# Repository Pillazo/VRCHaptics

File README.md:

# VRCHaptics
 VRC Haptics
A haptics set of software and hardware to give haptic feedback to VRChat on more than just your controllers. Old version used a melon-loader side-loaded dll file to pull bone positions out and set haptics. New version now uses the approved OSC system, by setting up the avatar in unity with 'VRC Contact Recievers'. A VB.NET program then grabs the OSC commands and then determines to turn on or off vibrating nodes you've mounted to yourself wherever!

A working example video here: https://youtu.be/_tgKSILLgIA

Node Assembly Video: https://youtu.be/x2D46sjlmms

Controller Assembly Video: https://youtu.be/UboYsb8L9xo

Controller Overview and use: https://youtu.be/rSFWYQzmyZ4

VB.Net program and use: https://youtu.be/C1V2dHkt9lk

Adding the Udon to your world: https://youtu.be/wW_y7pmaBFk

Find my project's discord at https://discord.gg/QjyNznq

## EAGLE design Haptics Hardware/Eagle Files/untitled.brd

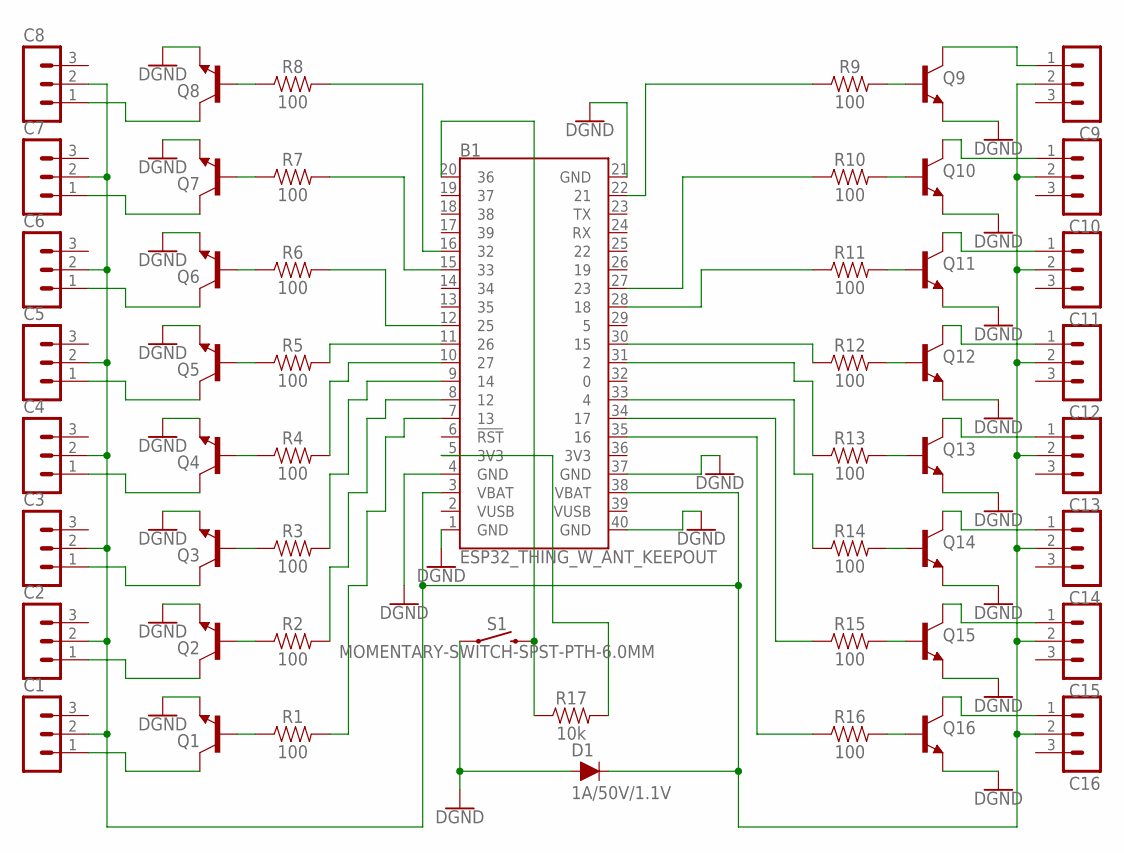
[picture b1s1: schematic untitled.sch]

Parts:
B1: ESP32_THING_W_ANT_KEEPOUT; ESP32_THING
C1, C2, C3, C4, C5, C6, C7, C8, C9, C10, C11, C12, C13, C14, C15, C16: MA03-1
D1: 1A/50V/1.1V; DIODE-1N4001
Q1, Q2, Q3, Q4, Q5, Q6, Q7, Q8, Q9, Q10, Q11, Q12, Q13, Q14, Q15, Q16: 600mA/40V; TO92-EBC
R1, R2, R3, R4, R5, R6, R7, R8, R9, R10, R11, R12, R13, R14, R15, R16: 100; AXIAL-0.1
R17: 10k; AXIAL-0.1
S1: MOMENTARY-SWITCH-SPST-PTH-6.0MM; TACTILE_SWITCH_PTH_6.0MM

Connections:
GND: B1.1 (GND), B1.4 (GND), B1.21 (GND), B1.37 (GND), B1.40 (GND), D1.A, Q1.E, Q2.E, Q3.E, Q4.E, Q5.E, Q6.E, Q7.E, Q8.E, Q9.E, Q10.E, Q11.E, Q12.E, Q13.E, Q14.E, Q15.E, Q16.E, S1.1
unnamed: B1.11 (26), R5.P$2 (2)
unnamed: B1.22 (21), R9.P$1 (1)
unnamed: Q9.B, R9.P$2 (2)
unnamed: B1.27 (23), R10.P$1 (1)
unnamed: B1.10 (27), R4.P$2 (2)
unnamed: B1.28 (18), R11.P$1 (1)
unnamed: B1.35 (16), R16.P$1 (1)
unnamed: B1.34 (17), R15.P$1 (1)
unnamed: B1.33 (4), R14.P$1 (1)
unnamed: Q16.B, R16.P$2 (2)
unnamed: Q15.B, R15.P$2 (2)
unnamed: Q14.B, R14.P$2 (2)
unnamed: Q13.B, R13.P$2 (2)
unnamed: Q12.B, R12.P$2 (2)
unnamed: Q11.B, R11.P$2 (2)
unnamed: Q10.B, R10.P$2 (2)
unnamed: B1.31 (2), R13.P$1 (1)
unnamed: B1.30 (15), R12.P$1 (1)
unnamed: Q2.B, R2.P$1 (1)
unnamed: Q1.B, R1.P$1 (1)
unnamed: Q3.B, R3.P$1 (1)
unnamed: Q4.B, R4.P$1 (1)
unnamed: Q5.B, R5.P$1 (1)
unnamed: Q6.B, R6.P$1 (1)
unnamed: Q7.B, R7.P$1 (1)
unnamed: Q8.B, R8.P$1 (1)
unnamed: C8.1, Q8.C
unnamed: C7.1, Q7.C
unnamed: C6.1, Q6.C
unnamed: C5.1, Q5.C
unnamed: C4.1, Q4.C
unnamed: C3.1, Q3.C
unnamed: C2.1, Q2.C
unnamed: C1.1, Q1.C
unnamed: C16.1, Q16.C
unnamed: C15.1, Q15.C
unnamed: C14.1, Q14.C
unnamed: C13.1, Q13.C
unnamed: C12.1, Q12.C
unnamed: C11.1, Q11.C
unnamed: C10.1, Q10.C
unnamed: C9.1, Q9.C
unnamed: B1.3 (VBAT), B1.38 (VBAT), C1.2, C2.2, C3.2, C4.2, C5.2, C6.2, C7.2, C8.2, C9.2, C10.2, C11.2, C12.2, C13.2, C14.2, C15.2, C16.2, D1.C
unnamed: B1.20 (36), R17.P$1 (1), S1.3 (2)
unnamed: B1.9 (14), R3.P$2 (2)
unnamed: B1.16 (32), R8.P$2 (2)
unnamed: B1.15 (33), R7.P$2 (2)
unnamed: B1.12 (25), R6.P$2 (2)
unnamed: B1.8 (12), R2.P$2 (2)
unnamed: B1.7 (13), R1.P$2 (2)
unnamed: B1.5 (3V3), R17.P$2 (2)

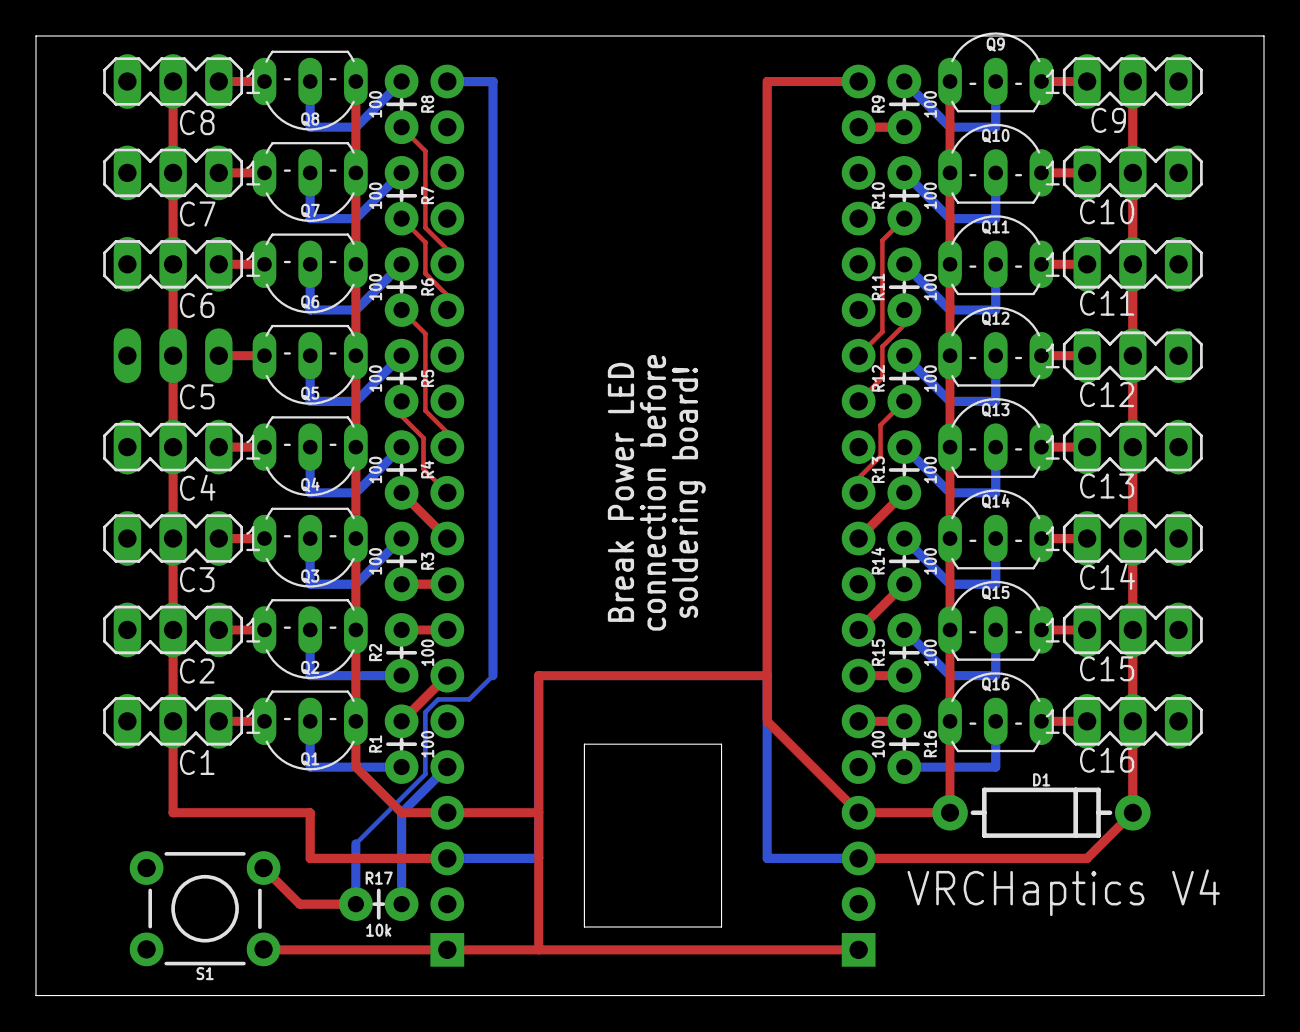
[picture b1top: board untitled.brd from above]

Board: 2 copper layers, 68.2 x 53.3 mm, 52 parts (1 on the bottom side), 52 nets.

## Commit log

2020-08-08 Solid Build
2020-08-08 Full Version 1
2020-08-08 Udon portion added
    Added a text file to directly copy - paste udon in, added reference pictures too
2020-08-09 August 9 2020 Update
    Continuing to update items, BOM, Icon, 3D print 3MFs
2020-08-09 BOM update and 3D update
    Added electronic components to BOM, added hole in the top of the main body so you could see LED.
2020-08-11 Cost Breakdown / BOM / New Node
    Cost breakdown added, BOM updated, new 0.75in node added
2020-08-12 Aug11-2020 Update
    Fix Controller factory reset
    add binary for controller
    add controller settings screenshots
    Fix live-controller error in VB.NET
2020-08-13 Commented Controller software
    Went through all the lines and commented it all
2020-08-14 VB.Net commented
    Like, it was already commented but, now its like, really commented.
2020-08-16 Hardware updated
    Added pictures for schematic and board layout for those without Eagle
2020-09-14 Debug Counters Added
    Debug counters added
2020-09-14 debug update 2
    changed richtextbox to textbox multiline
2020-09-14 Release version created
    Created release version
2020-09-14 Globilization change
    Added changing code for globilization decimal to comma conversion
2020-09-14 Fix globilization
    have to assign the output of the function @_@
2020-09-14 Removed some debug stuff
    Removed some debug stuff used to diagnose globilization
2021-11-26 MelonLoader update
    Changed to new MelonLoader DLL method, also added individualized force for each node.
2021-11-26 MelonLoader update
2021-11-27 Individual Node Testing and Improved Connection
    Added individual testing of nodes on the node DataGridView, as well as changing some UDP things on the ESP32 board.
2021-11-27 Hotfix lol
    Forgot to run program after removing that menu item, caused an error.
2021-11-28 Self touch update
    Added button to allow you to activate your own nodes to judge where to put them.
2021-12-06 UDP Issue update
    Turns out asking the VB.NET program to join a multicast group was bad? After I removed that the devices stopped disconnecting randomly.
2022-07-17 OSC Version
    This new version makes the program not illegal anymore lol. Takes out a ton of 3D stuff, now uses unity to add colliders that OSC reports to program to enable haptics.
2022-07-18 Delay Update
    Tried to add some indication the motor was turning on to the form, only added lag, so i commented that out
2022-07-18 Delay update 2
    forgot to clean out temp stuff...
2022-07-20 Haptics get stuck on fix
    Turns out having 2 timers was wrong, here's the fix.
2022-07-20 New Avatar JSON fix
    Turns out if a new avatar is selected, the JSON fixer needs to run, obviously. Duh.
2022-08-02 OctoSlime Test Update
    Addition of basic octoslime control
2022-09-07 Doge Example
    Doge dog example only for showing the VRC contacts

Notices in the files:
parts and their libraries:
SparkFun-Boards: Licensing: Creative Commons ShareAlike 4.0 International - https://creativecommons.org/licenses/by-sa/4.0
